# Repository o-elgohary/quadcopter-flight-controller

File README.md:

# Quadcopter Flight Controller

A 250mm-class quad flight controller, designed across three connected pieces: a custom PCB, a 3D-printed frame, and a control-systems simulation. None of this has been physically built or flown. It's a design and simulation project, stated plainly rather than implied otherwise.

## The integration story

The point of this project isn't any single piece, it's that each piece drove a real decision in another:

- **The simulation's control-loop speed requirement decided a wiring choice on the PCB.** The rate loop runs at 500Hz, which means the IMU needs to report data faster than 1kHz to keep up. That's why the ICM-42688-P is wired on SPI1 instead of I2C in the schematic, since I2C can't reliably keep pace with a loop that fast once you account for register-read overhead.
- **The PCB's real mounting-hole positions drove the CAD frame's geometry.** The board's STEP export (`pcb/exports/board.step`, once routing is finished) gets imported directly into the Fusion 360 frame model, and the center plate's mounting pattern is dimensioned straight off it, not measured by eye.
- **Every number in every phase traces back to one file, `spec.md`**, so a change to (say) the battery or frame size ripples outward instead of getting silently re-typed as a new assumption somewhere else.

## Repo layout

```
spec.md         master numbers every other file pulls from
pcb/            KiCad schematic + layout
cad/            exported Fusion 360 frame STEP
sim/            Python attitude-recovery simulation
```

## Status

| Phase | State |
|---|---|
| Spec (`spec.md`) | Done. Frame/motor/battery/IMU/MCU choices are real parts for this class of build; motor thrust/torque constants (kT, kQ) are documented estimates anchored to real bench-test data, not measured on this exact hardware. |
| PCB (`pcb/`) | Schematic done, ERC clean (0 errors, 2 benign warnings). Board outline, mounting holes, and component placement are done. Copper routing is not finished, so real DRC violations remain from auto-placement, left as the next real routing pass rather than papered over. |
| Frame (`cad/`) | Modeled in Fusion 360: center plate with the PCB's mounting pattern, 4 arms sized to the 250mm diagonal, motor mounts, battery deck. Exported to `cad/exports/frame_assembly.step`. Prop clearance checked analytically (adjacent motors clear by about 50mm at the prop tips). |
| Simulation (`sim/`) | A single-axis PD controller recovering a 20° tilt, settling in 0.13s. Deliberately simplified from an earlier, much larger 6-DOF version, see `sim/README.md` for why. Produces a plot (`sim/exports/recovery.png`). |

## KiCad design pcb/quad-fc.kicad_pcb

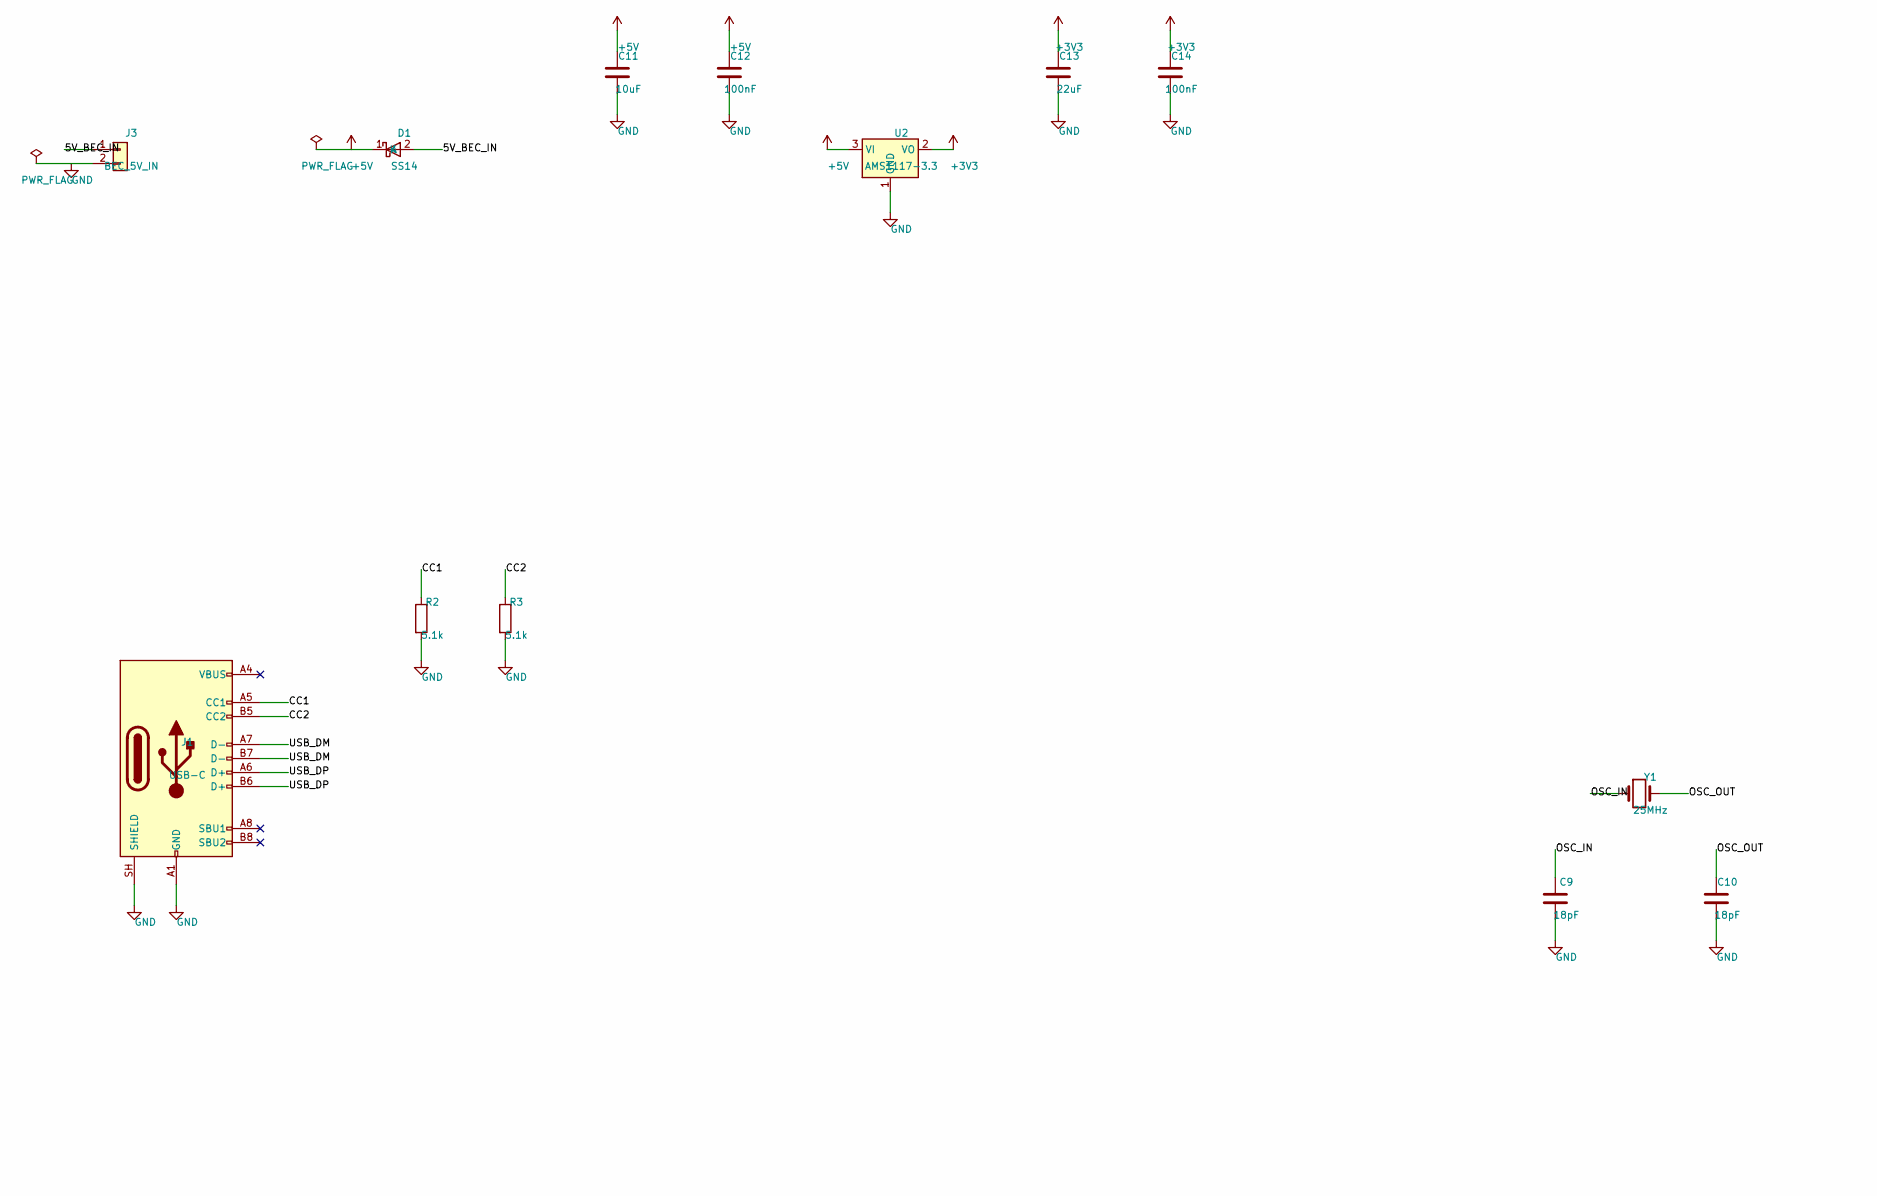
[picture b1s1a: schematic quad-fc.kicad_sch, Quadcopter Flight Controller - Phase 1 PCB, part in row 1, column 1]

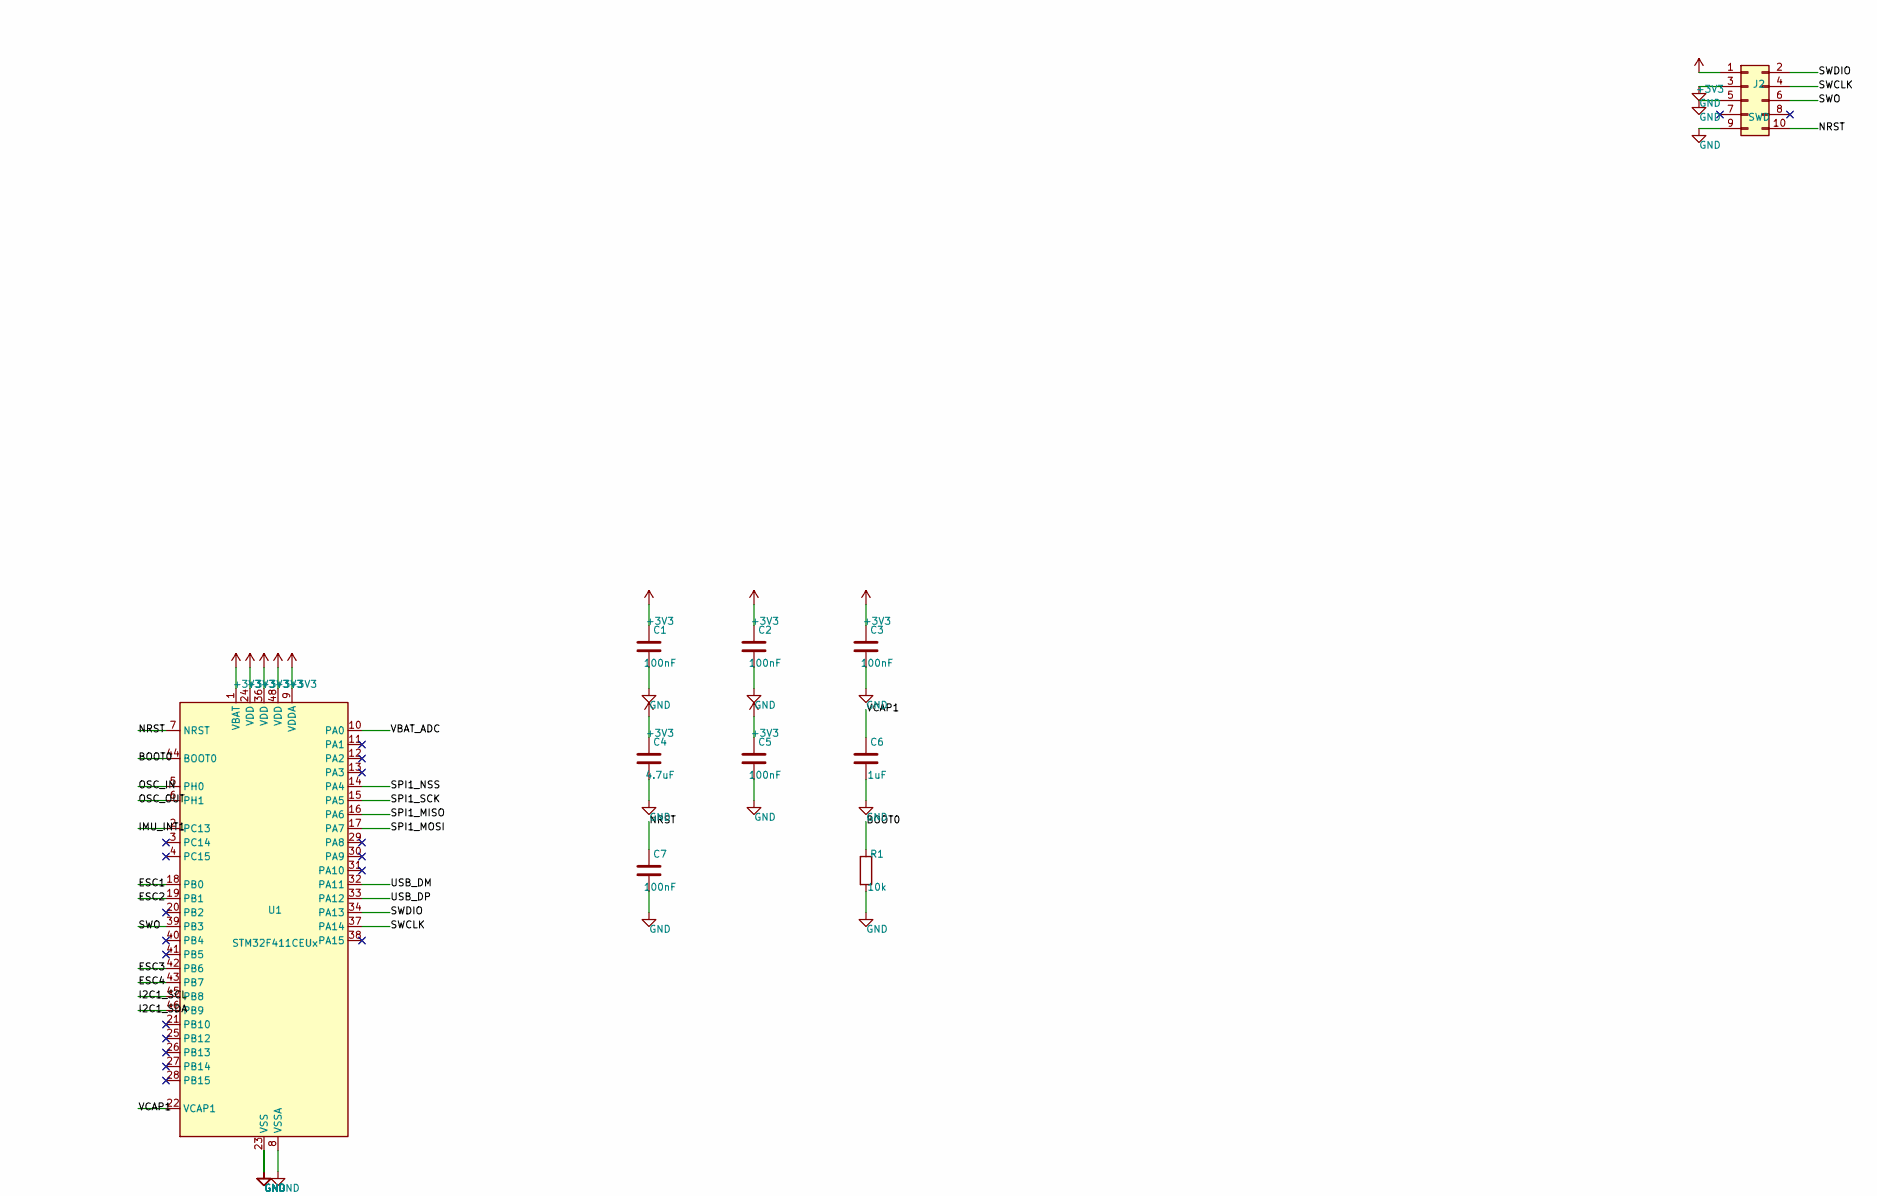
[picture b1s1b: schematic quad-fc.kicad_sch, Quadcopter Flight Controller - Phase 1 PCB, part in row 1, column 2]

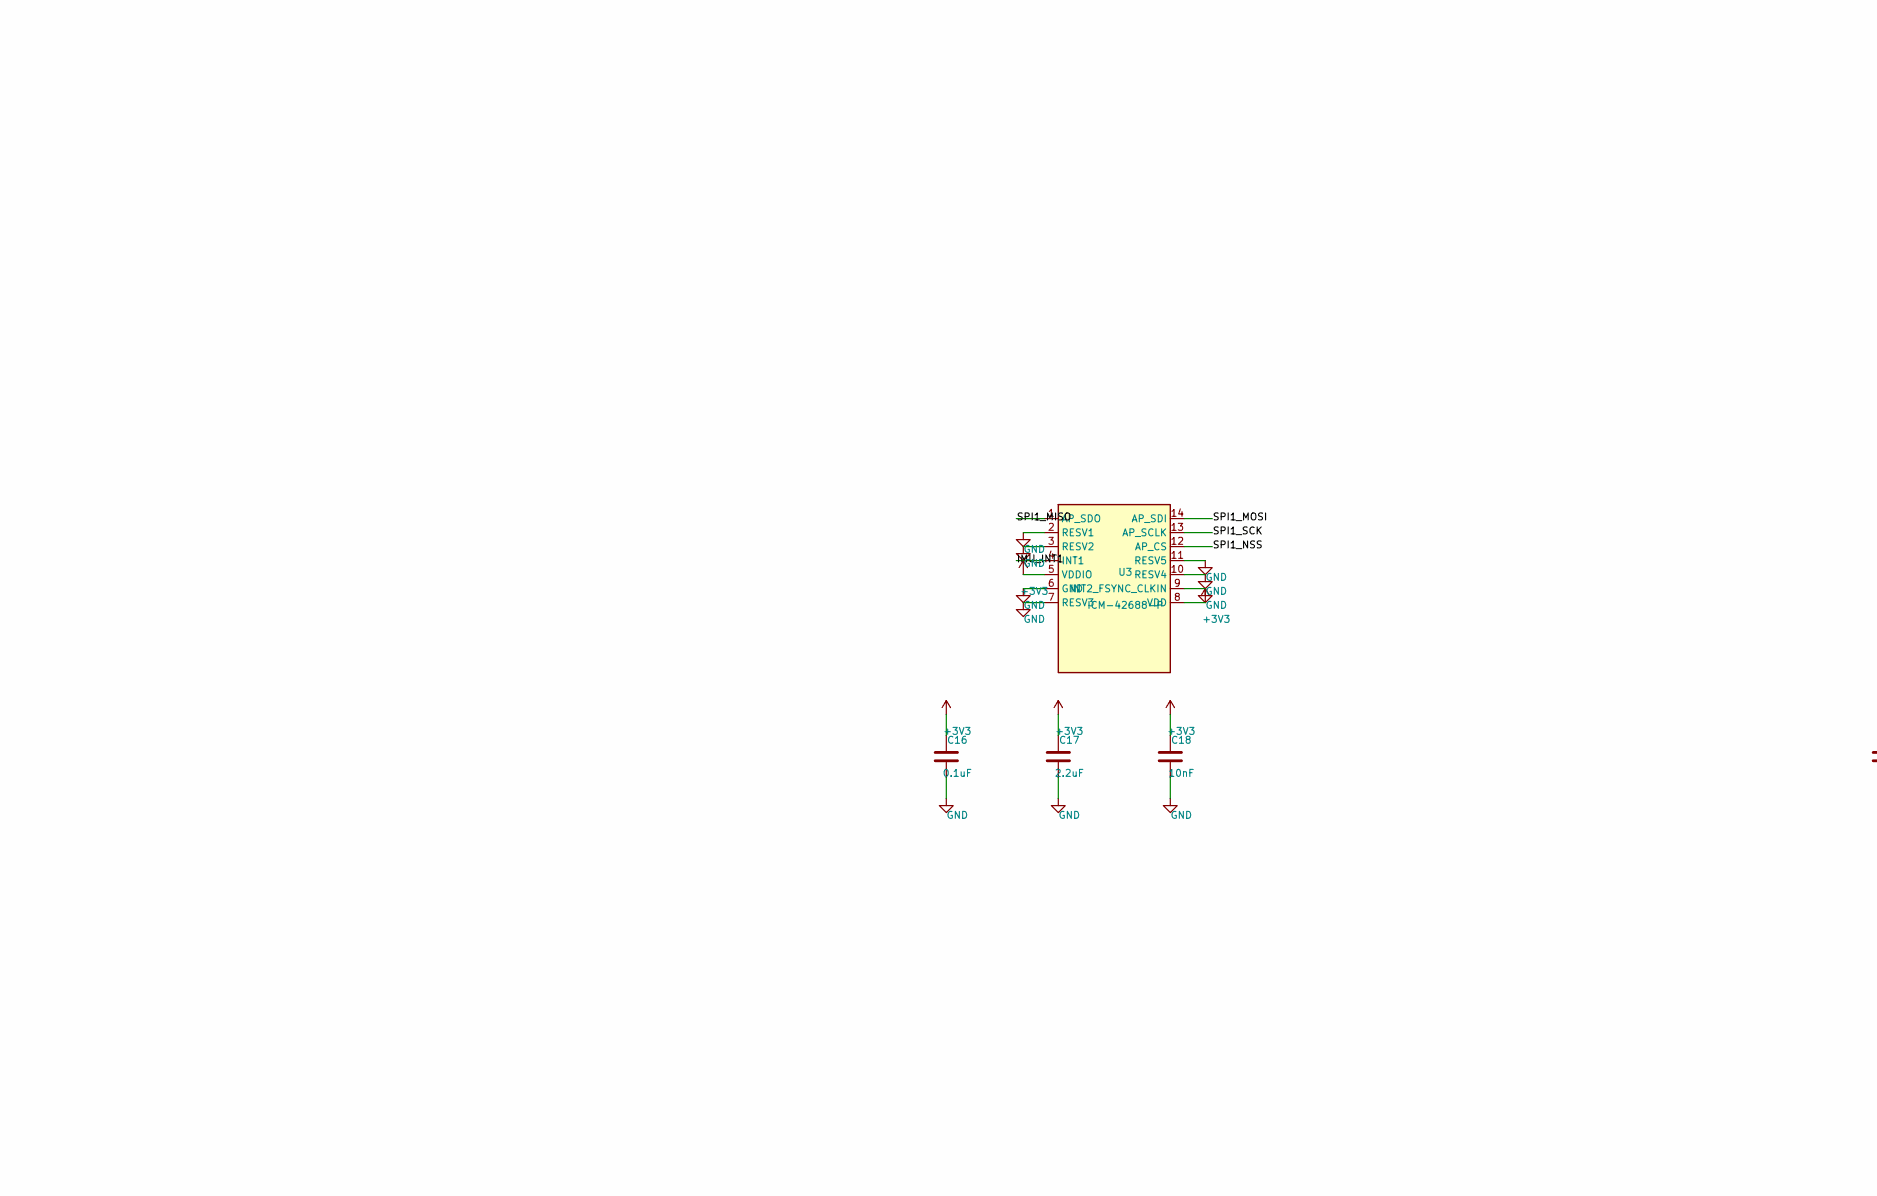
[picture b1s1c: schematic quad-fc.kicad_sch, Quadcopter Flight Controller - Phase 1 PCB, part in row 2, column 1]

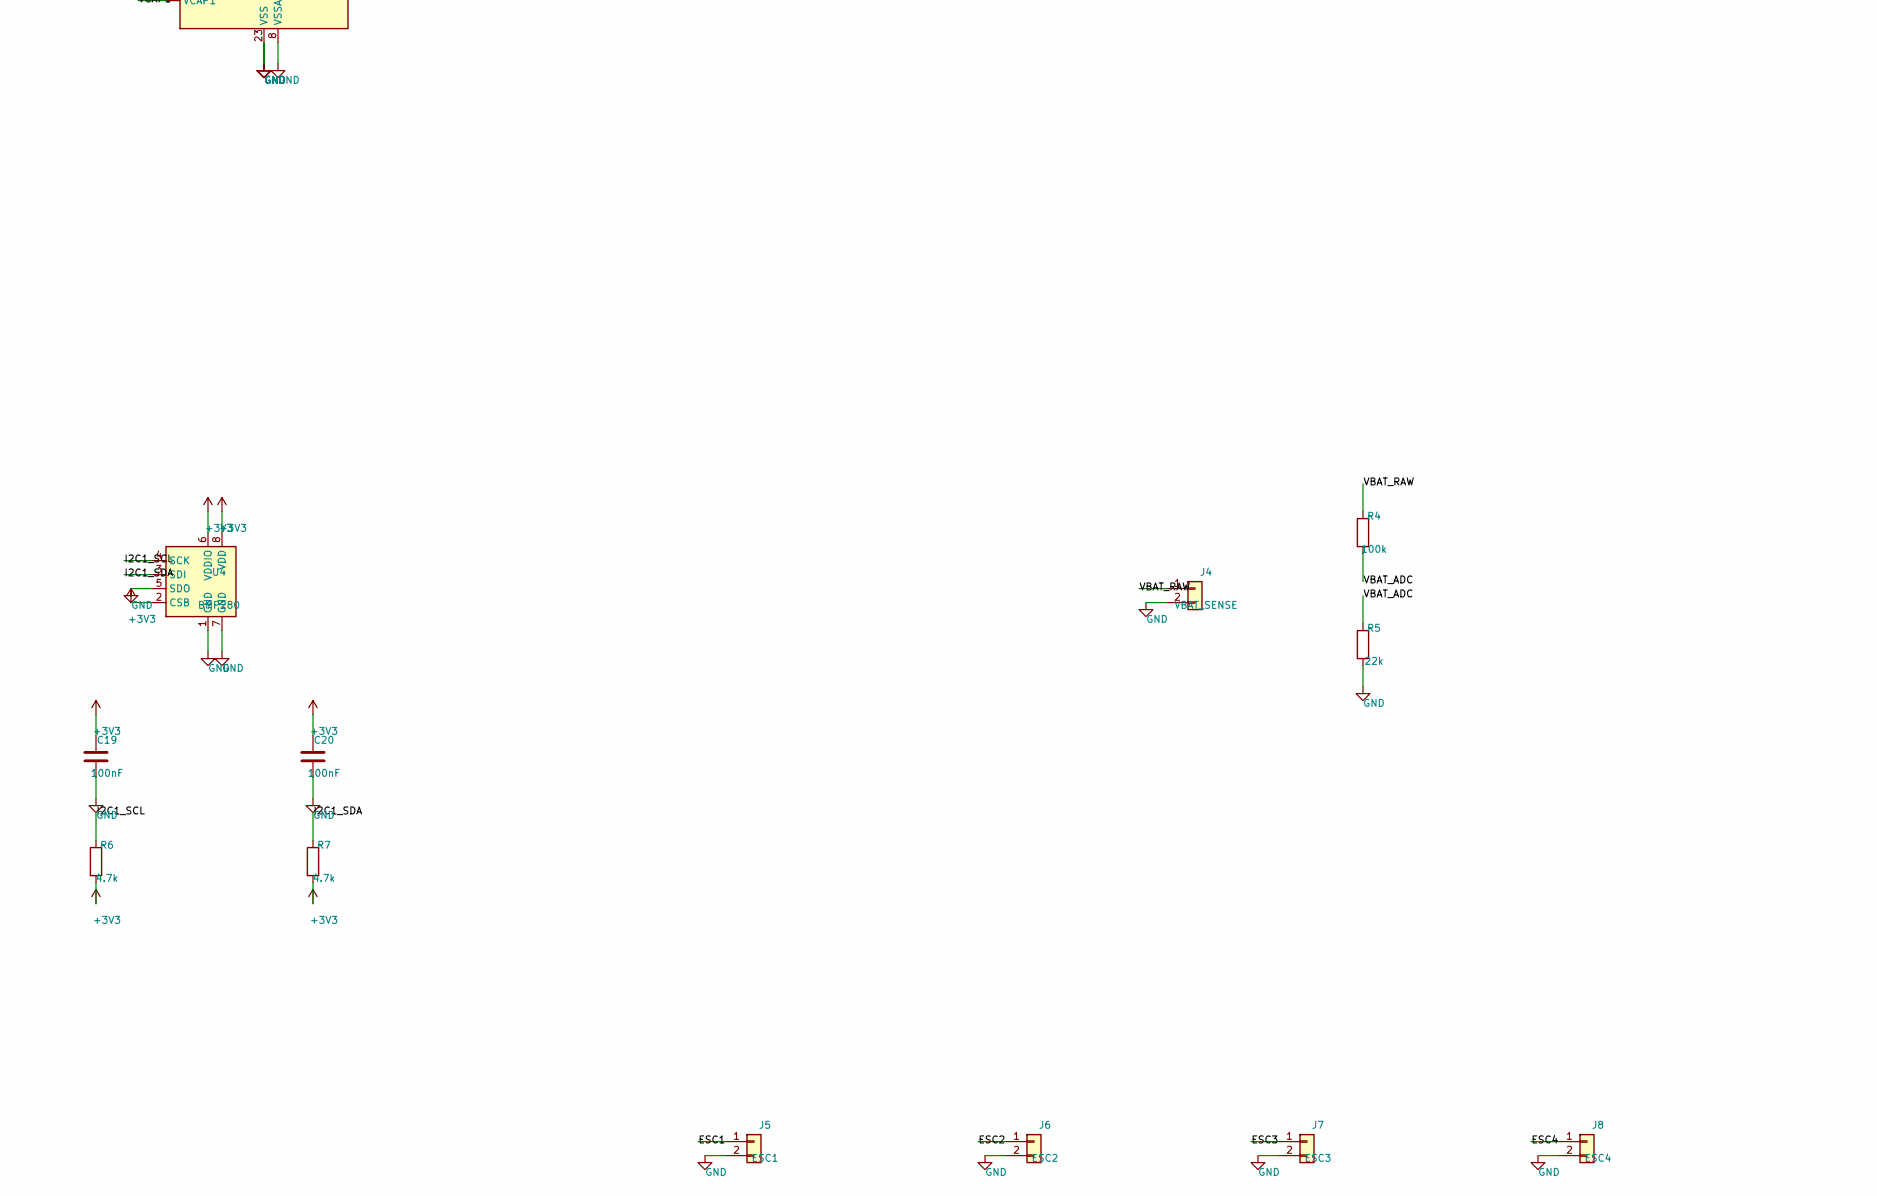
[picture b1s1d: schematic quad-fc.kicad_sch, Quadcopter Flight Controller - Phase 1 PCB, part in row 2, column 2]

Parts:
C1, C2, C3, C5, C7, C12, C14, C19, C20: 100nF; C_0603_1608Metric
C4: 4.7uF; C_0805_2012Metric
C6: 1uF; C_0603_1608Metric
C9, C10: 18pF; C_0603_1608Metric
C11: 10uF; C_0805_2012Metric
C13: 22uF; C_0805_2012Metric
C16: 0.1uF; C_0603_1608Metric
C17: 2.2uF; C_0805_2012Metric
C18: 10nF; C_0603_1608Metric
D1: SS14; D_SMA
J1: USB-C; USB_C_Receptacle_GCT_USB4105-xx-A_16P_TopMnt_Horizontal
J2: SWD; PinHeader_2x05_P1.27mm_Vertical
J3: BEC_5V_IN; PinHeader_1x02_P2.54mm_Vertical
J4: VBAT_SENSE; PinHeader_1x02_P2.54mm_Vertical
J5: ESC1; PinHeader_1x02_P2.54mm_Vertical
J6: ESC2; PinHeader_1x02_P2.54mm_Vertical
J7: ESC3; PinHeader_1x02_P2.54mm_Vertical
J8: ESC4; PinHeader_1x02_P2.54mm_Vertical
R1: 10k; R_0603_1608Metric
R2, R3: 5.1k; R_0603_1608Metric
R4: 100k; R_0603_1608Metric
R5: 22k; R_0603_1608Metric
R6, R7: 4.7k; R_0603_1608Metric
U1: STM32F411CEUx; QFN-48-1EP_7x7mm_P0.5mm_EP5.6x5.6mm
U2: AMS1117-3.3; SOT-223-3_TabPin2
U3: ICM-42688-P; LGA-14_3x2.5mm_P0.5mm_LayoutBorder3x4y
U4: BMP280; Bosch_LGA-8_2x2.5mm_P0.65mm_ClockwisePinNumbering
Y1: 25MHz; Crystal_SMD_3215-2Pin_3.2x1.5mm

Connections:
5V_BEC_IN: D1.2 (A), J3.1
+3V3: C1.1, C2.1, C3.1, C4.1, C5.1, C13.1, C14.1, C16.1, C17.1, C18.1, C19.1, C20.1, J2.1, R6.2, R7.2, U1.1 (VBAT), U1.9 (VDDA), U1.24 (VDD), U1.36 (VDD), U1.48 (VDD), U2.2 (VO), U3.5 (VDDIO), U3.8 (VDD), U4.2 (CSB), U4.6 (VDDIO), U4.8 (VDD)
+5V: C11.1, C12.1, D1.1 (K), U2.3 (VI)
BOOT0: R1.1, U1.44 (BOOT0)
CC1: J1.A5 (CC1), R2.1
CC2: J1.B5 (CC2), R3.1
ESC1: J5.1, U1.18 (PB0)
ESC2: J6.1, U1.19 (PB1)
ESC3: J7.1, U1.42 (PB6)
ESC4: J8.1, U1.43 (PB7)
GND: C1.2, C2.2, C3.2, C4.2, C5.2, C6.2, C7.2, C9.2, C10.2, C11.2, C12.2, C13.2, C14.2, C16.2, C17.2, C18.2, C19.2, C20.2, J1.A1 (GND), J1.A12 (GND), J1.B1 (GND), J1.B12 (GND), J1.SH (SHIELD), J2.3, J2.5, J2.9, J3.2, J4.2, J5.2, J6.2, J7.2, J8.2, R1.2, R2.2, R3.2, R5.2, U1.8 (VSSA), U1.23 (VSS), U1.35 (VSS), U1.47 (VSS), U1.49 (VSS), U2.1 (GND), U3.2 (RESV1), U3.3 (RESV2), U3.6 (GND), U3.7 (RESV3), U3.9 (INT2_FSYNC_CLKIN), U3.10 (RESV4), U3.11 (RESV5), U4.1 (GND), U4.5 (SDO), U4.7 (GND)
I2C1_SCL: R6.1, U1.45 (PB8), U4.4 (SCK)
I2C1_SDA: R7.1, U1.46 (PB9), U4.3 (SDI)
IMU_INT1: U1.2 (PC13), U3.4 (INT1)
NRST: C7.1, J2.10, U1.7 (NRST)
OSC_IN: C9.1, U1.5 (PH0), Y1.1
OSC_OUT: C10.1, U1.6 (PH1), Y1.2
SPI1_MISO: U1.16 (PA6), U3.1 (AP_SDO)
SPI1_MOSI: U1.17 (PA7), U3.14 (AP_SDI)
SPI1_NSS: U1.14 (PA4), U3.12 (AP_CS)
SPI1_SCK: U1.15 (PA5), U3.13 (AP_SCLK)
SWCLK: J2.4, U1.37 (PA14)
SWDIO: J2.2, U1.34 (PA13)
SWO: J2.6, U1.39 (PB3)
USB_DM: J1.A7 (D-), J1.B7 (D-), U1.32 (PA11)
USB_DP: J1.A6 (D+), J1.B6 (D+), U1.33 (PA12)
VBAT_ADC: R4.2, R5.1, U1.10 (PA0)
VBAT_RAW: J4.1, R4.1
VCAP1: C6.1, U1.22 (VCAP1)

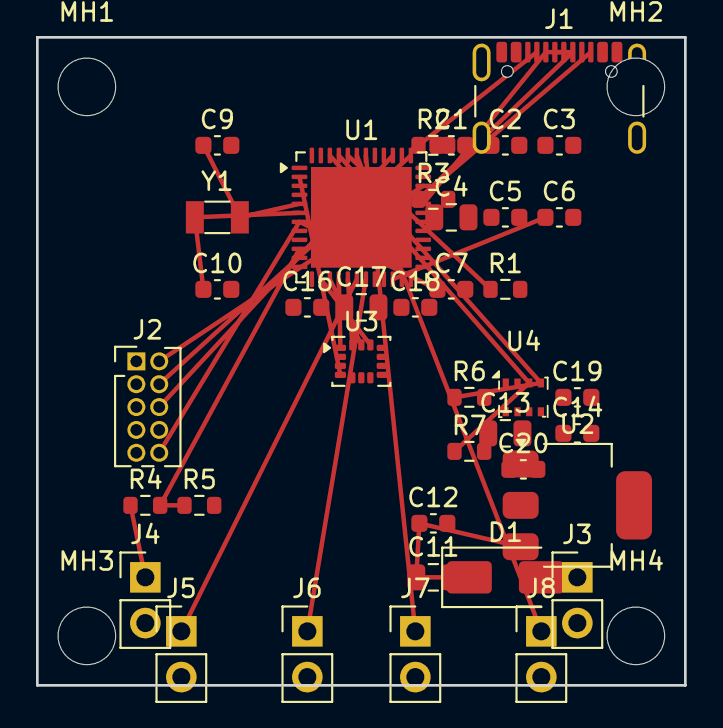
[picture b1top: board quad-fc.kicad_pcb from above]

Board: 2 copper layers, 36.0 x 36.0 mm, 43 parts (0 on the bottom side), 29 nets.

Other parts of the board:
MH1, MH2, MH3, MH4: M3; MountingHole_3.2mm_M3
